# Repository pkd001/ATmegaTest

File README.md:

View this project on [CADLAB.io](https://cadlab.io/project/2244). 

# ATmegaTest

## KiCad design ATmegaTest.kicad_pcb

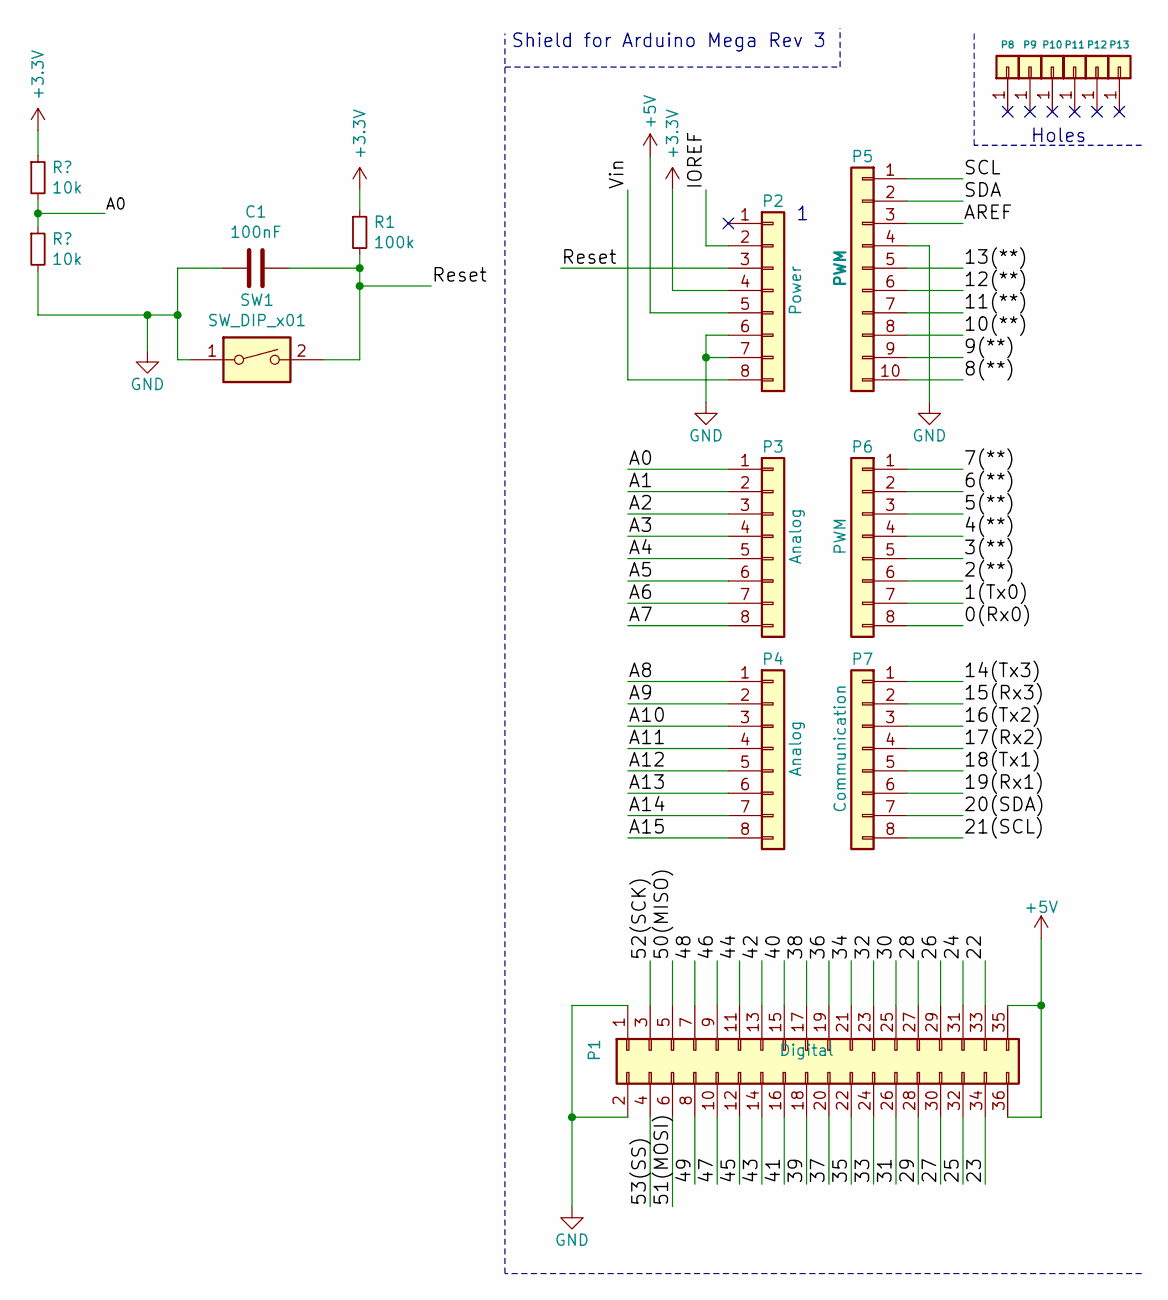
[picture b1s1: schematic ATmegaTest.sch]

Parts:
C1: 100nF; C_0603_1608Metric
P1: Digital; Socket_Strip_Arduino_2x18
P2: Power; Socket_Strip_Arduino_1x08
P3, P4: Analog; Socket_Strip_Arduino_1x08
P5: PWM; Socket_Strip_Arduino_1x10
P6: PWM; Socket_Strip_Arduino_1x08
P7: Communication; Socket_Strip_Arduino_1x08
P8, P9, P10, P11, P12, P13: CONN_01X01; Arduino_1pin
R1: 100k; R_0603_1608Metric
SW1: SW_DIP_x01

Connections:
+3V3: P2.4, R1.1; also elsewhere on the board
+5V: P1.35, P1.36, P2.5
/0(Rx0): P6.8
/1(Tx0): P6.7
/2(**): P6.6
/3(**): P6.5
/4(**): P6.4
/5(**): P6.3
/6(**): P6.2
/7(**): P6.1
/8(**): P5.10
/9(**): P5.9
/10(**): P5.8
/11(**): P5.7
/12(**): P5.6
/13(**): P5.5
/14(Tx3): P7.1
/15(Rx3): P7.2
/16(Tx2): P7.3
/17(Rx2): P7.4
/18(Tx1): P7.5
/19(Rx1): P7.6
/20(SDA): P7.7
/21(SCL): P7.8
/22: P1.33
/23: P1.34
/24: P1.31
/25: P1.32
/26: P1.29
/27: P1.30
/28: P1.27
/29: P1.28
/30: P1.25
/31: P1.26
/32: P1.23
/33: P1.24
/34: P1.21
/35: P1.22
/36: P1.19
/37: P1.20
/38: P1.17
/39: P1.18
/40: P1.15
/41: P1.16
/42: P1.13
/43: P1.14
/44: P1.11
/45: P1.12
/46: P1.9
/47: P1.10
/48: P1.7
/49: P1.8
/50(MISO): P1.5
/51(MOSI): P1.6
/52(SCK): P1.3
/53(SS): P1.4
/A0: P3.1; also elsewhere on the board
/A1: P3.2
/A2: P3.3
/A3: P3.4
/A4: P3.5
/A5: P3.6
/A6: P3.7
/A7: P3.8
/A8: P4.1
/A9: P4.2
/A10: P4.3
/A11: P4.4
/A12: P4.5
/A13: P4.6
/A14: P4.7
/A15: P4.8
/AREF: P5.3
/IOREF: P2.2
/Reset: C1.1, P2.3, R1.2, SW1.2
/SCL: P5.1
/SDA: P5.2
/Vin: P2.8
GND: C1.2, P1.1, P1.2, P2.6, P2.7, P5.4, SW1.1; also elsewhere on the board

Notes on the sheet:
Shield for Arduino Mega Rev 3
Holes

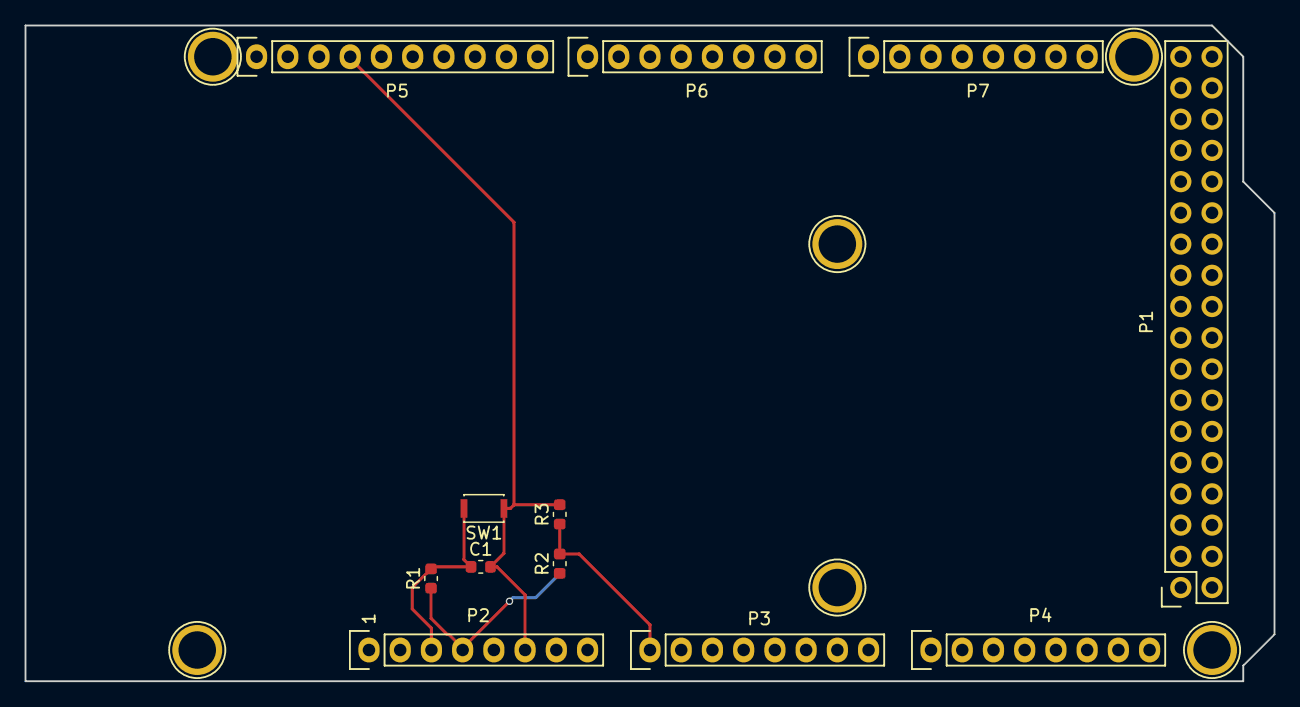
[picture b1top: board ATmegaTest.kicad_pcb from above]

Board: 2 copper layers, 101.6 x 53.3 mm, 18 parts (0 on the bottom side), 5 nets.

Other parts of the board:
R2, R3: 10k; R_0603_1608Metric

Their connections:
+3V3: R2.1; also elsewhere on the board
/A0: R2.2, R3.1; also elsewhere on the board
GND: R3.2; also elsewhere on the board

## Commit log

2019-10-25 Create fp-info-cache
2019-10-25 Backlink to CADLAB.io has been added.
2019-10-25 symbolDisplayIssue
    updated Libraries and resaved
2019-10-25 Removal
    observe effects based on removing project specific libraries
2019-10-25 To Ignore
    to reduce possibilities of individual files backup and commited to Renote
    repo
2019-10-25 RESET ckt
    reset circuit for uC
2019-10-26 gitignore
    cache file
2019-10-26 library change
    location changed
2019-10-26 Update fp-info-cache
    footprintRemoved
2019-10-28 DividerCkt
    Voltage Divider with analogInput to ATMEGA
2019-10-28 DividerCkt
    PCB changes as per SchematicDividerCkt
2019-10-31 Revert "DividerCkt"
    This reverts commit aaad2765e5774504384bd17e4f9678753ffa88e0.
2019-10-31 Revert "DividerCkt"
    This reverts commit 058e6e4fb967e27780ca64c39ae31b78ca90827e.
